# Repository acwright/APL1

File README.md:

APL1
====

A homebrew **Apple 1** replica built around the **6502** microprocessor, with a modern microcontroller-based terminal that adds PS/2 keyboard and serial input alongside the original ASCII keyboard interface.

---

## Table of Contents

- [Overview](#overview)
- [Architecture](#architecture)
- [Hardware](#hardware)
  - [APL1 Board](#apl1-board)
    - [Revision History](#revision-history)
- [Firmware](#firmware)
  - [APL1 Controller](#apl1-controller)
  - [APL1 ROM](#apl1-rom)
  - [APL1 Terminal](#apl1-terminal)
- [CAD](#cad)
- [Production](#production)
- [Schematics](#schematics)
- [Libraries](#libraries)
- [Bill of Materials](#bill-of-materials)
- [License](#license)

---

## Overview

The **APL1** is a faithful recreation of the 1976 Apple 1 computer, rebuilt as an open-source KiCad project. It preserves the original 6502 + PIA architecture and the classic [WozMon](https://en.wikipedia.org/wiki/Woz_Monitor) firmware experience, while replacing the bulky discrete terminal section of the original with an ATmega1284 microcontroller. The MCU emulates the Apple 1 keyboard and display handshake exactly, but also exposes a PS/2 keyboard port and a serial terminal connection for modern convenience.

## Architecture

- **CPU**: MOS 6502 running at 1 MHz
- **RAM**: 32KB SRAM (AS6C62256)
- **ROM**: 8KB EEPROM (28C64) holding WozMon
- **PIA**: 65C21 — the Apple 1 keyboard/display interface
- **Terminal**: ATmega1284(P) controller emulating the original terminal handshake
- **Input**: Original ASCII keyboard header, PS/2 keyboard, and serial (RS-232) input
- **Output**: Serial terminal output, with composite video reserved for a future revision
- **Bus**: 16-bit address bus, 8-bit bidirectional data bus, standard 6502 control signals
- **Clock**: 1 MHz oscillator for the 6502; 28.63636 MHz crystal (8× NTSC colorburst) for the controller

## Hardware

This repository contains KiCad 7.0+ PCB designs for the APL1 board.

### APL1 Board
`Hardware/APL1/`

The single board hosting the 6502 CPU, memory, PIA, and the ATmega1284 terminal controller. Provides:

- **CPU**: 6502 running at 1 MHz
- **RAM**: 32KB SRAM (AS6C62256)
- **ROM**: 8KB EEPROM (28C64) preloaded with WozMon
- **PIA**: 65C21 keyboard/display interface (original Apple 1 footprint)
- **Terminal Controller**: ATmega1284(P) running APL1 Controller firmware
- **Keyboard buffer**: 74LS245 octal bus transceiver
- **Glue logic**: 74LS04, 74LS00, and 74LS138 address decoder
- **Serial**: MAX232 level shifter with DB-9 (DTE) connector
- **Input**: Original ASCII keyboard header and PS/2 keyboard connector
- **Video**: RCA composite video jack (reserved for a future firmware revision)
- **Reset**: Keyboard reset and clear controls handled by the controller
- **Power**: 5V DC via barrel jack, with power switch and indicator LED

#### Revision History

**Rev 1.1**

- Add 10k pull-down resistor `R9` for KBDCLR.
- Change pull-up resistors `R1-R4` from 1k to 4.7k.
- Add capacitor `C17` for bulk capacitance at power supply.

**Rev 1.0**

- Initial release.

## Firmware

This repository contains firmware for the terminal controller, the system ROM, and the desktop terminal application.

### APL1 Controller
`Firmware/APL1 Controller/`

[PlatformIO](https://platformio.org/)-based firmware for the ATmega1284(P) terminal controller. Provides:

- Faithful emulation of the Apple 1 keyboard and display handshake (DA / RDAB)
- Original ASCII keyboard pass-through via the 74LS245 buffer
- PS/2 keyboard input with a custom Set-2 ISR decoder mapped to Apple 1 ASCII
- Serial (RS-232) terminal input and output at 115200 8N1
- Control shortcuts for clear screen, reset, and throttle ("slow") mode
- Keyboard reset and clear button handling
- Composite video output hooks reserved for a future revision

See [Firmware/APL1 Controller/README.md](./Firmware/APL1%20Controller/README.md) for build, flash, and pin-map details.

### APL1 ROM
`Firmware/APL1 ROM/`

The system ROM image built from **WozMon**, Steve Wozniak's original Apple 1 monitor, assembled with the [cc65](https://cc65.github.io/) toolchain and burned to a 28C64 EEPROM.

See [Firmware/APL1 ROM/README.md](./Firmware/APL1%20ROM/README.md) for build and programming instructions.

### APL1 Terminal
`Firmware/APL1-Terminal/`

An [Electron](https://www.electronjs.org/) + [Vue 3](https://vuejs.org/) desktop application that provides a faithful CRT terminal experience for the APL1. Connects to the board over the DB-9 serial port at 115200 8N1 and renders output using the original Signetics 2513 character ROM glyphs. Provides:

- 40×24 character canvas rendered with the authentic Signetics 2513 font
- Selectable phosphor color: white, amber, or green
- CRT effects: phosphor glow, scanlines overlay, and screen flicker animation
- Serial port connection and disconnection (auto-detected ports)
- Keyboard input forwarded to the APL1 with Apple 1 control shortcuts (Ctrl+L clear, Ctrl+\ reset, Ctrl+T throttle)
- Built-in program loader with paced character/line sending for 20 bundled Wozmon programs
- Settings panel with per-character and per-line delay controls
- macOS (Apple Silicon DMG), Linux (AppImage / deb), and Windows (NSIS installer) distribution builds, all built locally from macOS

See [Firmware/APL1-Terminal/README.md](./Firmware/APL1-Terminal/README.md) for build and run instructions.

## CAD
`CAD/`

3D models and images for the APL1 board and its components.

## Production
`Production/`

JLCPCB-ready fabrication files, BOM, and component positions for PCB fabrication and assembly.

## Schematics
`Schematics/`

Schematics for the APL1 board.

## Libraries
`Libraries/`

Shared KiCad symbol and footprint libraries used across the APL1 hardware project.

## Bill of Materials

| Reference | Qty | Value | Description |
|-----------|-----|-------|-------------|
| C1–C10 | 10 | 100nF | Disc Capacitor |
| C11, C14, C15, C16 | 4 | 1µF | Disc Capacitor |
| C12, C13 | 2 | 18pF | Disc Capacitor |
| C31 | 1 | 10uF | Electrolytic Capacitor 16v |
| D1 | 1 | POWER LED | 3.0mm Power LED |
| J2 | 1 | KEYBOARD | ASCII Keyboard Header (DIP-16) |
| J3 | 1 | SERIAL (DTE) | DB-9 Male |
| J4 | 1 | 5V DC | DC Barrel Jack |
| J5 | 1 | PS/2 | 6-pin Mini-DIN (KMDGX-6S-BS) |
| J6 | 1 | VIDEO | RCA Jack (PJRAN1X1U0XX) |
| R1–R4 | 4 | 4.7kΩ | 1/8W Resistor |
| R6 | 1 | 1kΩ | 1/8W Resistor |
| R5 | 1 | 330Ω | 1/8W Resistor |
| R7, R8 | 2 | 820Ω | 1/8W Resistor |
| R9 | 2 | 10kΩ | 1/8W Resistor |
| SW1 | 1 | POWER | SPDT Switch (400MSP1R6BLKM6QE) |
| U1 | 1 | 74LS04 | Hex Inverter |
| U2 | 1 | 6502 | 6502 CPU |
| U3 | 1 | 65C21 | PIA |
| U4 | 1 | AS6C62256 | 32KB SRAM |
| U5 | 1 | 74LS00 | Quad NAND |
| U6 | 1 | 74LS138 | 3-to-8 Decoder |
| U7 | 1 | 28C64 | 8KB EEPROM |
| U8 | 1 | 74LS245 | Octal Bus Transceiver |
| U9 | 1 | MAX232 | RS-232 Transceiver |
| U10 | 1 | ATmega1284-P | Terminal Controller MCU |
| Y1 | 1 | 1MHz | DIP-14 Oscillator |
| Y2 | 1 | 28.636MHz | Crystal |

## License

Hardware designs are released under the [CERN Open Hardware Licence Version 2 – Permissive](https://ohwr.org/cern_ohl_p_v2.txt).

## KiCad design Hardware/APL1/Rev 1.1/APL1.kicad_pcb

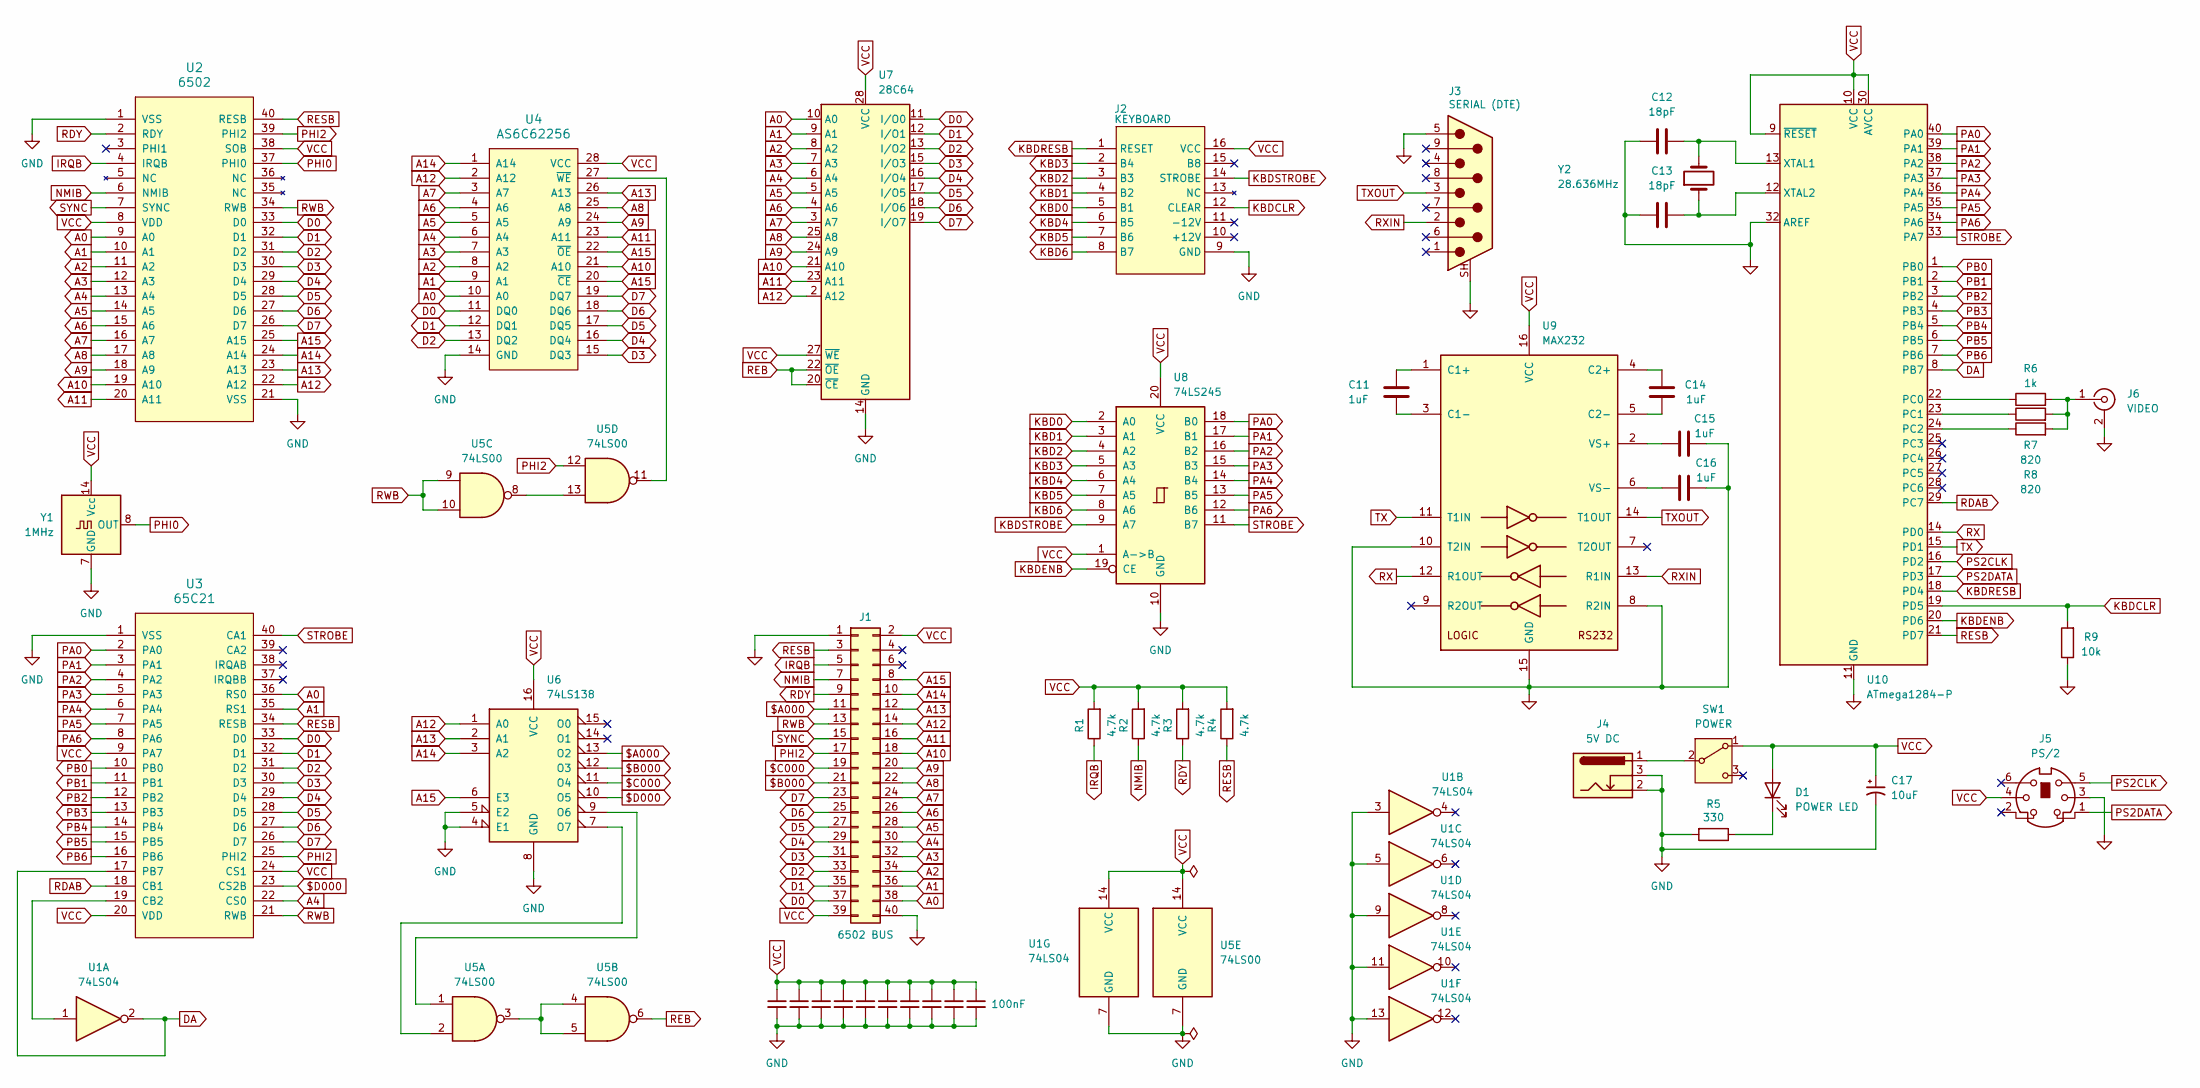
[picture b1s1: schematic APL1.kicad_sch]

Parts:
C1, C2, C3, C4, C5, C6, C7, C8, C9, C10: 100nF; C_Disc_D5.0mm_W2.5mm_P5.00mm
C11, C14, C15, C16: 1uF; C_Disc_D5.0mm_W2.5mm_P5.00mm
C12, C13: 18pF; C_Disc_D5.0mm_W2.5mm_P5.00mm
C17: 10uF; CP_Radial_D4.0mm_P1.50mm
D1: POWER LED; LED_D3.0mm; Digikey 732-5008-ND
J1: 6502 BUS; 6502 Bus Connector
J2: KEYBOARD; DIP-16_W7.62mm_Socket_LongPads
J3: SERIAL (DTE); DSUB-9_Pins_Horizontal_P2.77x2.84mm_EdgePinOffset7.70mm_Hou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; MPN D09P33E4GX00LF; Digikey 609-1481-ND
J4: 5V DC; BarrelJack_Horizontal; Digikey 2073-DCJ200-10-A-K1-K-ND
J5: PS/2; KMDGX-6S-BS
J6: VIDEO; SWITCHCRAFT_PJRAN1X1U0XX
R1, R2, R3, R4: 4.7k; R_Axial_DIN0207_L6.3mm_D2.5mm_P10.16mm_Horizontal
R5: 330; R_Axial_DIN0207_L6.3mm_D2.5mm_P10.16mm_Horizontal
R6: 1k; R_Axial_DIN0207_L6.3mm_D2.5mm_P10.16mm_Horizontal
R7, R8: 820; R_Axial_DIN0207_L6.3mm_D2.5mm_P10.16mm_Horizontal
R9: 10k; R_Axial_DIN0207_L6.3mm_D2.5mm_P10.16mm_Horizontal
SW1: POWER; SW_400MSP1R6BLKM6QE; Digikey EG4326-ND
U1: 74LS04; DIP-14_W7.62mm_Socket_LongPads
U2: 6502; DIP-40_W15.24mm_Socket_LongPads
U3: 65C21; DIP-40_W15.24mm_Socket_LongPads
U4: AS6C62256; DIP-28_W15.24mm_Socket_LongPads
U5: 74LS00; DIP-14_W7.62mm_Socket_LongPads
U6: 74LS138; DIP-16_W7.62mm_Socket_LongPads
U7: 28C64; DIP-28_W15.24mm_Socket_LongPads
U8: 74LS245; DIP-20_W7.62mm_Socket_LongPads
U9: MAX232; DIP-16_W7.62mm_Socket_LongPads; Digikey 296-1402-5-ND
U10: ATmega1284-P; DIP-40_W15.24mm_Socket_LongPads
Y1: 1MHz; Oscillator_DIP-14
Y2: 28.636MHz; Crystal_HC49-U_Vertical; Digikey 887-1256-ND

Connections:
$A000: J1.11, U6.13 (O2)
$B000: J1.21, U6.12 (O3)
$C000: J1.19, U6.11 (O4)
$D000: U3.23 (CS2B), U6.10 (O5)
A0: J1.38, U2.9 (A0), U3.36 (RS0), U4.10 (A0), U7.10 (A0)
A1: J1.36, U2.10 (A1), U3.35 (RS1), U4.9 (A1), U7.9 (A1)
A2: J1.34, U2.11 (A2), U4.8 (A2), U7.8 (A2)
A3: J1.32, U2.12 (A3), U4.7 (A3), U7.7 (A3)
A4: J1.30, U2.13 (A4), U3.22 (CS0), U4.6 (A4), U7.6 (A4)
A5: J1.28, U2.14 (A5), U4.5 (A5), U7.5 (A5)
A6: J1.26, U2.15 (A6), U4.4 (A6), U7.4 (A6)
A7: J1.24, U2.16 (A7), U4.3 (A7), U7.3 (A7)
A8: J1.22, U2.17 (A8), U4.25 (A8), U7.25 (A8)
A9: J1.20, U2.18 (A9), U4.24 (A9), U7.24 (A9)
A10: J1.18, U2.19 (A10), U4.21 (A10), U7.21 (A10)
A11: J1.16, U2.20 (A11), U4.23 (A11), U7.23 (A11)
A12: J1.14, U2.22 (A12), U4.2 (A12), U6.1 (A0), U7.2 (A12)
A13: J1.12, U2.23 (A13), U4.26 (A13), U6.2 (A1)
A14: J1.10, U2.24 (A14), U4.1 (A14), U6.3 (A2)
A15: J1.8, U2.25 (A15), U4.20 (~CE), U4.22 (~OE), U6.6 (E3)
D0: J1.37, U2.33 (D0), U3.33 (D0), U4.11 (DQ0), U7.11 (I/O0)
D1: J1.35, U2.32 (D1), U3.32 (D1), U4.12 (DQ1), U7.12 (I/O1)
D2: J1.33, U2.31 (D2), U3.31 (D2), U4.13 (DQ2), U7.13 (I/O2)
D3: J1.31, U2.30 (D3), U3.30 (D3), U4.15 (DQ3), U7.15 (I/O3)
D4: J1.29, U2.29 (D4), U3.29 (D4), U4.16 (DQ4), U7.16 (I/O4)
D5: J1.27, U2.28 (D5), U3.28 (D5), U4.17 (DQ5), U7.17 (I/O5)
D6: J1.25, U2.27 (D6), U3.27 (D6), U4.18 (DQ6), U7.18 (I/O6)
D7: J1.23, U2.26 (D7), U3.26 (D7), U4.19 (DQ7), U7.19 (I/O7)
DA: U1.2, U3.17 (PB7), U10.8 (PB7)
GND: C1.2, C2.2, C3.2, C4.2, C5.2, C6.2, C7.2, C8.2, C9.2, C10.2, C12.1, C13.1, C15.1, C16.1, C17.2, J1.1, J1.40, J2.9 (GND), J3.5, J3.SH (PAD), J4.2, J4.3, J5.3, J6.2 (Ext), R5.2, R9.1, U1.3, U1.5, U1.7 (GND), U1.9, U1.11, U1.13, U2.1 (VSS), U2.21 (VSS), U3.1 (VSS), U4.14 (GND), U5.7 (GND), U6.4 (E1), U6.5 (E2), U6.8 (GND), U7.14 (GND), U8.10 (GND), U9.8 (R2IN), U9.10 (T2IN), U9.15 (GND), U10.11 (GND), U10.31 (GND), U10.32 (AREF), Y1.7 (GND)
IRQB: J1.5, R1.1, U2.4 (IRQB)
KBD0: J2.5 (B1), U8.2 (A0)
KBD1: J2.4 (B2), U8.3 (A1)
KBD2: J2.3 (B3), U8.4 (A2)
KBD3: J2.2 (B4), U8.5 (A3)
KBD4: J2.6 (B5), U8.6 (A4)
KBD5: J2.7 (B6), U8.7 (A5)
KBD6: J2.8 (B7), U8.8 (A6)
KBDCLR: J2.12 (CLEAR), R9.2, U10.19 (PD5)
KBDENB: U8.19 (CE), U10.20 (PD6)
KBDRESB: J2.1 (RESET), U10.18 (PD4)
KBDSTROBE: J2.14 (STROBE), U8.9 (A7)
NMIB: J1.7, R2.1, U2.6 (NMIB)
unnamed: D1.1 (K), R5.1
unnamed: J6.1 (In), R6.2, R7.2, R8.2
unnamed: J4.1, SW1.2 (B)
unnamed: U1.1, U3.19 (CB2)
unnamed: U4.27 (~WE), U5.11
unnamed: U5.3, U5.4, U5.5
unnamed: U5.8, U5.13
unnamed: U5.1, U6.9 (O6)
unnamed: U5.2, U6.7 (O7)
unnamed: C11.1, U9.1 (C1+)
unnamed: C11.2, U9.3 (C1-)
unnamed: C14.2, U9.4 (C2+)
unnamed: C14.1, U9.5 (C2-)
unnamed: C15.2, U9.2 (VS+)
unnamed: C16.2, U9.6 (VS-)
unnamed: R6.1, U10.22 (PC0)
unnamed: R7.1, U10.23 (PC1)
unnamed: R8.1, U10.24 (PC2)
unnamed: C12.2, U10.13 (XTAL1), Y2.2
unnamed: C13.2, U10.12 (XTAL2), Y2.1
PA0: U3.2 (PA0), U8.18 (B0), U10.40 (PA0)
PA1: U3.3 (PA1), U8.17 (B1), U10.39 (PA1)
PA2: U3.4 (PA2), U8.16 (B2), U10.38 (PA2)
PA3: U3.5 (PA3), U8.15 (B3), U10.37 (PA3)
PA4: U3.6 (PA4), U8.14 (B4), U10.36 (PA4)
PA5: U3.7 (PA5), U8.13 (B5), U10.35 (PA5)
PA6: U3.8 (PA6), U8.12 (B6), U10.34 (PA6)
PB0: U3.10 (PB0), U10.1 (PB0)
PB1: U3.11 (PB1), U10.2 (PB1)
PB2: U3.12 (PB2), U10.3 (PB2)
PB3: U3.13 (PB3), U10.4 (PB3)
PB4: U3.14 (PB4), U10.5 (PB4)
PB5: U3.15 (PB5), U10.6 (PB5)
PB6: U3.16 (PB6), U10.7 (PB6)
PHI0: U2.37 (PHI0), Y1.8 (OUT)
PHI2: J1.17, U2.39 (PHI2), U3.25 (PHI2), U5.12
PS2CLK: J5.5, U10.16 (PD2)
PS2DATA: J5.1, U10.17 (PD3)
RDAB: U3.18 (CB1), U10.29 (PC7)
RDY: J1.9, R3.1, U2.2 (RDY)
REB: U5.6, U7.20 (~CE), U7.22 (~OE)
RESB: J1.3, R4.1, U2.40 (RESB), U3.34 (RESB), U10.21 (PD7)
RWB: J1.13, U2.34 (RWB), U3.21 (RWB), U5.9, U5.10
RX: U9.12 (R1OUT), U10.14 (PD0)
RXIN: J3.2, U9.13 (R1IN)
STROBE: U3.40 (CA1), U8.11 (B7), U10.33 (PA7)
SYNC: J1.15, U2.7 (SYNC)
TX: U9.11 (T1IN), U10.15 (PD1)
TXOUT: J3.3, U9.14 (T1OUT)
VCC: C1.1, C2.1, C3.1, C4.1, C5.1, C6.1, C7.1, C8.1, C9.1, C10.1, C17.1, D1.2 (A), J1.2, J1.39, J2.16 (VCC), J5.4, R1.2, R2.2, R3.2, R4.2, SW1.1 (A), U1.14 (VCC), U2.8 (VDD), U2.38 (SOB), U3.9 (PA7), U3.20 (VDD), U3.24 (CS1), U4.28 (VCC), U5.14 (VCC), U6.16 (VCC), U7.27 (~WE), U7.28 (VCC), U8.1 (A->B), U8.20 (VCC), U9.16 (VCC), U10.9 (~RESET), U10.10 (VCC), U10.30 (AVCC), Y1.14 (Vcc)

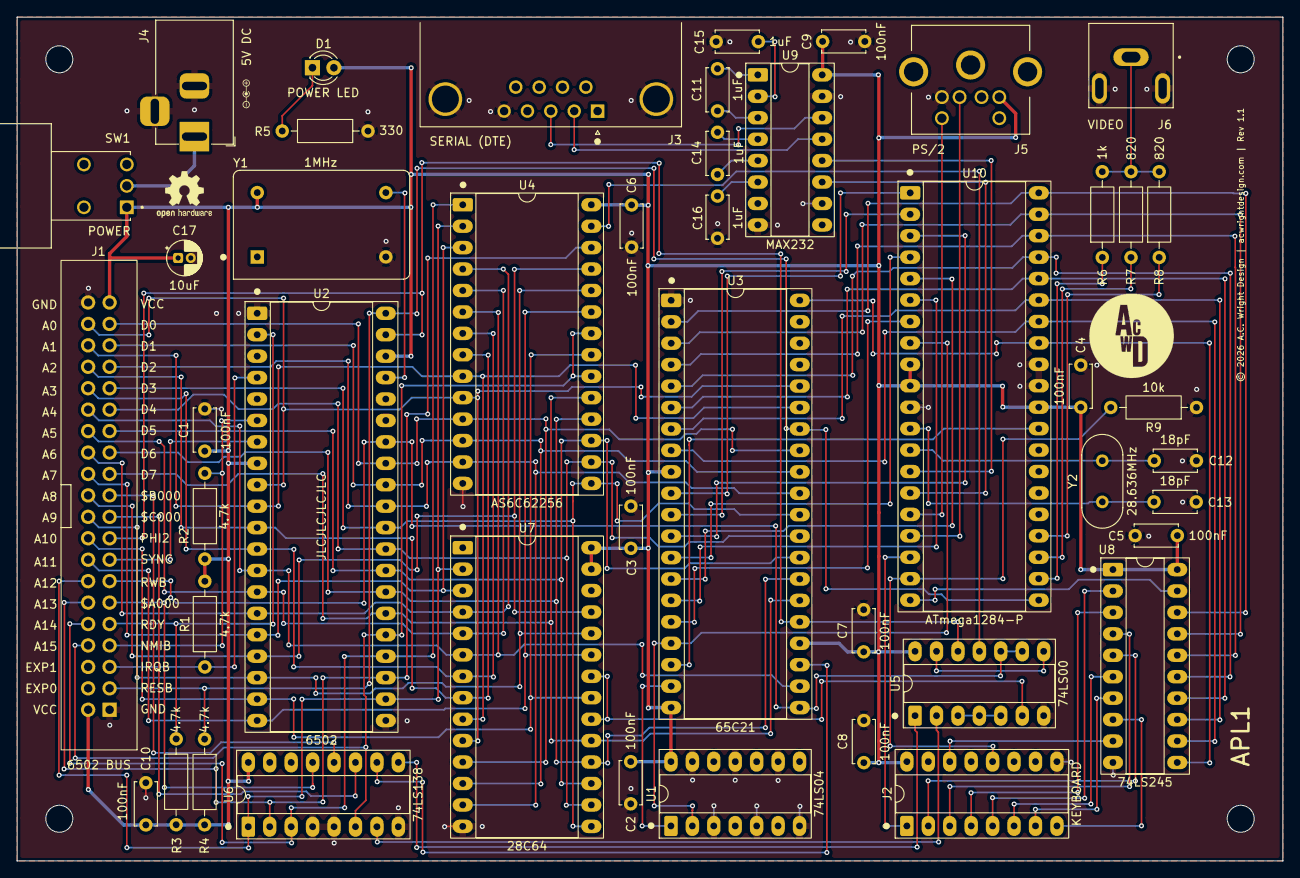
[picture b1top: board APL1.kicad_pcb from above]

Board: 2 copper layers, 150.0 x 100.0 mm, 46 parts (0 on the bottom side), 93 nets.

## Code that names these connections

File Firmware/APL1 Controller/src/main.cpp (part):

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// Port / pin macros
// ---------------------------------------------------------------------------

// PORTA  PA0-6 = keyboard ASCII data to PIA PA0-6; PA7 = STROBE (CA1)
//        Idle = Hi-Z input (driven only while injecting a key)
#define PA_DATA_MASK    0x7F
#define PA_STROBE_BIT   7

// PORTB  PB0-6 = display data from PIA; PB7 = DA (display available)
//        The PIA CB2 handshake output is active-LOW, but it passes through an
//        external 74HC04 inverter (U1) before reaching PB7, so at the ATmega
//        DA is active-HIGH: PB7 HIGH = 6502 has written a char (DA asserted).
#define PB_DISP_MASK    0x7F
#define PB_DA_BIT       7

// PORTC  PC0-2 = video DAC outputs (deferred, kept low)
//        PC3-6 = unused inputs w/ pullup
//        PC7   = RDAB -> CB1 (active-low pulse; idle HIGH)
#define PC_DAC_MASK     0x07
#define PC_RDAB_BIT     7
#define PC_RDAB_LOW()   (PORTC &= ~(1 << PC_RDAB_BIT))
#define PC_RDAB_HIGH()  (PORTC |=  (1 << PC_RDAB_BIT))

// PORTD  PD0=RXD  PD1=TXD  PD2=PS2CLK(INT0)  PD3=PS2DATA
//        PD4=KBDRESB(in,active-low)  PD5=KBDCLR(in,active-HIGH)
//        PD6=KBDENB(out,active-low: LOW=74LS245 enabled)
//        PD7=RESB(out,active-low reset to 6502)
#define PD_RXD_BIT      0
#define PD_TXD_BIT      1
#define PD_PS2CLK_BIT   2
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// ---------------------------------------------------------------------------
// ascii : Apple-1 style (bit7 set, uppercase).
//   1. Disable 74LS245 so PA bus is not contended.
//   2. Drive PA0-6 = data, PA7 (STROBE) starts LOW.
//   3. Rising edge on PA7 latches data into PIA CA1.
//   4. Return PA to Hi-Z, re-enable buffer.
void sendKey(uint8_t ascii) {
    KBDENB_DISABLE();                           // PD6 HIGH – disable 74LS245

    DDRA  = 0xFF;                               // PA all outputs
    PORTA = ascii & PA_DATA_MASK;               // PA0-6 = data; PA7 (STROBE) LOW
    delayMicroseconds(2);                       // data setup time

    PORTA |=  (1 << PA_STROBE_BIT);            // PA7 HIGH → rising edge on CA1
    delayMicroseconds(20);                      // PIA latch hold time
    PORTA &= ~(1 << PA_STROBE_BIT);            // PA7 LOW
    delayMicroseconds(2);

    DDRA  = 0x00;                               // PA back to Hi-Z inputs
    PORTA = 0x00;

    KBDENB_ENABLE();                            // PD6 LOW – re-enable 74LS245
}

// ---------------------------------------------------------------------------
// PS/2 frame ISR  (INT0, triggered on falling edge of PS2CLK/PD2)
//   11-bit frame: start(0) | D0..D7 LSB-first | parity(odd) | stop(1)
// ---------------------------------------------------------------------------
ISR(INT0_vect) {
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    DDRA  = 0x00;
    PORTA = 0x00;

    // --- PORTB: all inputs. DA (PB7) is driven by the 74HC04 (U1) output, so no
    //     pull-up is used: an internal pull-up would force PB7 HIGH and, because
    //     DA is active-HIGH here, register as a permanent (false) DA assertion.
    DDRB  = 0x00;
    PORTB = 0x00;               // no pull-ups; U1 actively drives DA, PIA drives PB0-6

    // --- PORTC ---
    // PC0-2 = outputs (video DAC, deferred), drive LOW
    // PC3-6 = unused inputs with pullup (defined state)
    // PC7   = output, idle HIGH (RDAB)
    DDRC  = (1 << PC_RDAB_BIT) | PC_DAC_MASK;    // 0x87
    PORTC = (1 << PC_RDAB_BIT)                    // RDAB idle HIGH
          | (1 << 3) | (1 << 4) | (1 << 5) | (1 << 6); // PC3-6 pullups; 0xF8 total

    // --- PORTD ---
    // PD0 = RXD input  (UART)
    // PD1 = TXD output (UART)
    // PD2-5 = inputs; PS2CLK, PS2DATA, KBDRESB have pullup; KBDCLR has NO pullup
    //   (KBDCLR is active-HIGH: idle LOW, goes HIGH when key pressed)
    // PD6 = KBDENB output, start LOW (74LS245 buffer enabled)
    // PD7 = RESB  output, start LOW (6502 held in reset)
    DDRD  = (1 << PD_TXD_BIT) | (1 << PD_KBDENB_BIT) | (1 << PD_RESB_BIT); // 0xC2
    PORTD = (1 << PD_PS2CLK_BIT) | (1 << PD_PS2DATA_BIT)
          | (1 << PD_KBDRESB_BIT);
    // KBDCLR (PD5) = 0 → no pullup; PD6 (KBDENB) = 0 → enabled; PD7 (RESB) = 0 → 6502 in reset  (0x1C)

    Serial.begin(115200);   // init UART before releasing 6502 reset

    // --- Power-on reset: hold RESB low, then release ---
    delay(10);       // 10 ms – allows supply rails to stabilise
    RESB_RELEASE();  // PD7 HIGH – release 6502 from reset

    // --- PS/2: INT0 on PD2 falling edge ---
    EICRA = (EICRA & ~0x03) | (1 << ISC01);   // ISC01=1, ISC00=0 = falling edge
    EIMSK |= (1 << INT0);                      // enable INT0
}
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void loop() {
    // --- Display path (PIA -> serial) ---
    // DA is active-HIGH at the ATmega (PIA CB2 is active-low but inverted by U1):
    // PB7 HIGH means the 6502 has written a char to the PIA.
    if (PINB & (1 << PB_DA_BIT)) {
        uint8_t c = PINB & PB_DISP_MASK;       // read PB0-6 (bit7 = DA, ignored)

        // Throttle mode: leave DA asserted so the 6502 keeps spinning in its
        // output-polling loop, replicating the original terminal's slow rate.
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    // --- Control signals (KBDRESB active-low / KBDCLR active-high, debounced) ---
    // KBDRESB: arm on falling edge, fire if still LOW after 20 ms.
    // KBDCLR:  arm on rising  edge, fire if still HIGH after 20 ms.
    // NOTE: KBDCLR (PD5) requires an external ~10 kΩ pull-down resistor to GND.
    //       Without it the pin floats HIGH and button presses cannot be detected.
    {
        static uint8_t  resb_prev  = 1, clr_prev   = 0;
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        static uint32_t resb_t     = 0, clr_t      = 0;
        static bool     clr_init   = false;    // snapshot pin on first tick

        uint8_t resb = (PIND >> PD_KBDRESB_BIT) & 1;
        uint8_t clr  = (PIND >> PD_KBDCLR_BIT)  & 1;

        // Initialise clr_prev to the actual pin state so a floating-HIGH pin
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
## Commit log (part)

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2026-05-26 Update to schematic
2026-05-27 Layout PCB
2026-05-28 Finish PCB
2026-05-28 Update schematic
2026-06-02 Add APL1 Controller firmware
2026-06-04 Finish firmware and add README and manuals
2026-06-06 CAD for base
2026-06-07 Change KBDCLRB to KBDCLR (active high)
2026-06-07 Add APL1 image
2026-06-07 Fix image link
2026-06-07 Add R9 to BOM
2026-06-07 Firmware fix
2026-06-07 Firmware fix for 74HCT245 handling
2026-06-07 Add Terminal firmware
2026-06-07 fix: CI distutils and space-in-path for electron-builder
2026-06-07 fix: use --break-system-packages for pip on CI runners
2026-06-07 fix: add repository field for electron-builder GitHub publish
2026-06-07 fix: run electron-vite build before electron-builder
2026-06-07 Initial plan
2026-06-07 Fix Linux package maintainer metadata
2026-06-07 Add logo
2026-06-07 fix: add author email for deb, split mac builds by arch
2026-06-07 Add logo files
2026-06-08 Update firmware folder names
2026-06-08 Remove Mac x64 build from release workflow
2026-06-08 Linux-only CI; add release:mac script for local mac builds
2026-06-08 Fix release workflow: build with --publish never, upload via gh CLI
2026-06-08 Disable CSC auto-discovery on mac CI runner to fix 504
2026-06-08 Bump actions to Node.js 22 to fix deprecation warnings
2026-06-08 Track build assets (icon) in git; fix missing icon in CI builds
2026-06-08 Enable Developer ID signing and notarization in CI
2026-06-08 Fix notarize config: use boolean for electron-builder 26.x
2026-06-08 Fix: use APPLE_APP_SPECIFIC_PASSWORD env var for notarization
2026-06-08 Bump checkout and setup-node to v5 to fix Node.js 20 deprecation warnings
2026-06-08 Add software and UI fixes
2026-06-08 Improved UI redraw
2026-06-11 Add Terminal README
2026-06-15 Fix silkscreen and add bulk capacitance
2026-06-15 README fix
2026-06-18 Add Rev 1.1

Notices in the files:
Hardware/APL1/Rev 1.1/APL1.kicad_pcb:
© 2026 A.C. Wright Design | acwrightdesign.com | Rev 1.1
